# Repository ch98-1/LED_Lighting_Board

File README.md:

# LED_Lighting_Board
 DC to DC LED panel board with 5v input voltage. Made for smd reflow practice.
 takes 2.8v to 5.5v for input.

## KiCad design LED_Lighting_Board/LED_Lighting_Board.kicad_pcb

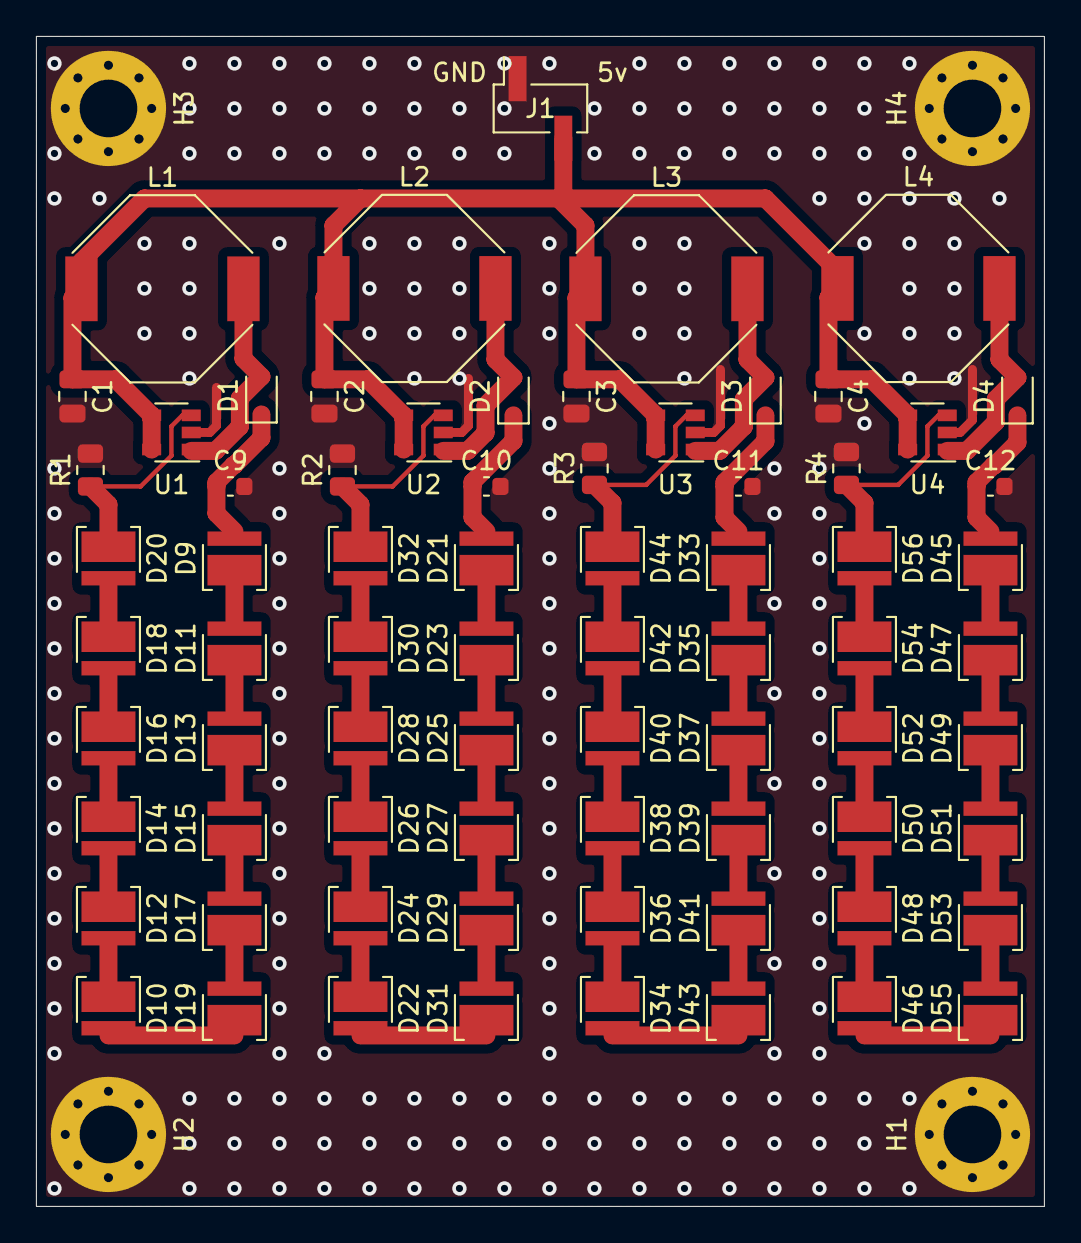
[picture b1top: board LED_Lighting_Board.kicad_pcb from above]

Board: 2 copper layers, 56.0 x 65.0 mm, 77 parts (0 on the bottom side), 58 nets.

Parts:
C1, C2, C3, C4: 10u; C_0805_2012Metric
C9, C10, C11, C12: 1u; C_0603_1608Metric
D1, D2, D3, D4: D_Schottky; D_SOD-323
D9, D10, D11, D12, D13, D14, D15, D16, D17, D18, D19, D20, D21, D22, D23, D24, D25, D26, D27, D28, D29, D30, D31, D32, D33, D34, D35, D36, D37, D38, D39, D40, D41, D42, D43, D44, D45, D46, D47, D48, D49, D50, D51, D52, D53, D54, D55, D56: LED; LED_Cree-XH
H1, H2, H3, H4: MountingHole_Pad; MountingHole_3.2mm_M3_Pad_Via
J1: Conn_01x02; PinHeader_1x02_P2.54mm_Vertical_SMD_Pin1Right
L1, L2, L3, L4: 47u; L_Bourns-SRU1028_10.0x10.0mm
R1, R2, R3, R4: 10; R_0805_2012Metric
U1, U2, U3, U4: CAT4238; SOT-23-5

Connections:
+5V: C1.1, C2.1, C3.1, C4.1, J1.2, L1.1, L2.1, L3.1, L4.1, U1.4, U1.5, U2.4, U2.5, U3.4, U3.5, U4.4, U4.5
GND: C1.2, C2.2, C3.2, C4.2, C9.2, C10.2, C11.2, C12.2, H1.1, H2.1, H3.1, H4.1, J1.1, R1.2, R2.2, R3.2, R4.2, U1.2, U2.2, U3.2, U4.2
unnamed: C9.1, D1.1, D9.2
unnamed: C10.1, D2.1, D21.2
unnamed: C11.1, D3.1, D33.2
unnamed: C12.1, D4.1, D45.2
unnamed: D1.2, L1.2, U1.1
unnamed: D2.2, L2.2, U2.1
unnamed: D3.2, L3.2, U3.1
unnamed: D4.2, L4.2, U4.1
unnamed: D10.1, D12.2
unnamed: D10.2, D19.1
unnamed: D11.1, D13.2
unnamed: D9.1, D11.2
unnamed: D12.1, D14.2
unnamed: D13.1, D15.2
unnamed: D14.1, D16.2
unnamed: D15.1, D17.2
unnamed: D16.1, D18.2
unnamed: D17.1, D19.2
unnamed: D18.1, D20.2
unnamed: D20.1, R1.1, U1.3
unnamed: D21.1, D23.2
unnamed: D22.1, D24.2
unnamed: D22.2, D31.1
unnamed: D23.1, D25.2
unnamed: D24.1, D26.2
unnamed: D25.1, D27.2
unnamed: D26.1, D28.2
unnamed: D27.1, D29.2
unnamed: D28.1, D30.2
unnamed: D29.1, D31.2
unnamed: D30.1, D32.2
unnamed: D32.1, R2.1, U2.3
unnamed: D33.1, D35.2
unnamed: D34.1, D36.2
unnamed: D34.2, D43.1
unnamed: D35.1, D37.2
unnamed: D36.1, D38.2
unnamed: D37.1, D39.2
unnamed: D38.1, D40.2
unnamed: D39.1, D41.2
unnamed: D40.1, D42.2
unnamed: D41.1, D43.2
unnamed: D42.1, D44.2
unnamed: D44.1, R3.1, U3.3
unnamed: D45.1, D47.2
unnamed: D46.1, D48.2
unnamed: D46.2, D55.1
unnamed: D47.1, D49.2
unnamed: D48.1, D50.2
unnamed: D49.1, D51.2
unnamed: D50.1, D52.2
unnamed: D51.1, D53.2
unnamed: D52.1, D54.2
unnamed: D53.1, D55.2
unnamed: D54.1, D56.2
unnamed: D56.1, R4.1, U4.3

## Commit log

2021-10-24 Finished the board
2022-01-20 moved BOM
